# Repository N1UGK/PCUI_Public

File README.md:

# PCUI (Pocket Computer Universal Interface)
This is the official repo for firmware updates for the PCUI, owners manuals, and general information.  Further, this repo contains a collection of programs for various pocket computers and calculators supported by the PCUI.

## Development History

https://n1ugk.com/2025/12/pocket-computer-universal-interface/

## Features Summary

+ Provides cassette interface emulation to read and write programs and data directly to and from a micro SD card.
+ Provides a printer interface between the pocket computer or calculator and most standard “line printers” such as dot matrix, thermal receipt printers, serial, parallel, and Wi-Fi.
+ Supports printing of custom glyphs, including math, scientific and engineering symbols unique to each model.
+ Works independently without a computer and can be powered by a single 18650 lithium ion rechargeable battery.
+ OLED screen with user-friendly menu system and operating modes
+ Interface packs provide connectivity to each supported model, no need for OEM connection cables.
+ Updatable firmware and PC or Mac connectivity via USB for mounting micro SD card
+ Plotter emulation mode to provide printouts of plots using modern printers allowing programs which leveraged plotter features to be used on modern printers.
+ ASCII BASIC conversion to tokenized BASIC “on the fly”, allowing for program edits and program creation on a Mac or PC and directly sending it to a pocket computer.
+ Wi-Fi connectivity and web interface for program viewing, editing, UI control, printing, and status.
+ Online program library browsing and installing directly from GitHub allows you to view community released programs for various models of pocket computers directly from the PCUI.
+ True low-level cassette interface integration - byte level retrieval and storage of programs and data images, not just a simple "record" and "playback" mechanism.

## Supported Models

The following models are currently supported with more models in progress:

+ Texas Instruments	Graph Link Graphing Calculators
  + TI-82*, TI-85*, TI-86*, TI-89*, TI-92*, TI-92 Plus*, Voyage 200*
+ Sharp 9-pin “CE-121” / “CE-122” Compatibles
  + PC-1210, PC-1211, PC-1212, TRS-80 PC-1*
+ Sharp	Older 11-pin “CE-126P” Compatibles
  + PC-1245, PC-1246, PC-1246S, PC-1247, PC-1248, Tandy PC-8*
  + PC-1250, PC-1250A, PC-1251, PC-1251H, PC-1255, Tandy PC-3* and PC-3 A/B*, PC-1270
+ 11-pin “CE-126P” Compatibles
  + PC-1260, PC-1280
+ Sharp	Newer 11-pin “CE-126P” Compatibles
  + PC-1401, PC-1403*, PC-1421, PC-1430, PC-1450, EL-5500, EL-5500 II, EL-5500III*
+ Casio	12-pin PB-100 Series FP-12(S) Compatibles
  + PB-100, PB-110, PB-120, PB-200, PB-400, PB-410*, FX-700P, FX-710P, Tandy PC-4 Version B*, TRS-80 PC-4 Version A*
+ Casio	12-pin FX “Clamshell” Series
  + FX-770P, FX-780P, FX-781P, FX-785P, FX-790P, FX-791P, FX-795P, Tandy PC-5*, Tandy PC-6*
+ Casio	15-pin “FA-10” Compatibles
  + PB-700*, PB-770*
+ Casio	FX-702P*, FX-602P*

_*Tested and Verified, others should work since they use the same interface_

The PCUI Owners manual can be found in the [Documentation](./Documentation/) folder.

Firmware updates can be found in the [Firmware](./Firmware/) folder.

## Purchasing a Kit or Fully Assembled PCUI

A PCUI can be purchased as a kit or fully assembled.  

+ PCUI Kit - includes pre-flashed Pico 2 W, Main PCB and all components.  Interface pack kits are add-ons.  
  + Assembly instructions are located in the [Documentation](./Documentation/) folder.
  + The BOM, 3D model, KiCad Projects are located in the [Hardware](./Hardware/) folder.
+ PCUI Fully Assembled - includes a fully assembled PCUI and chosen interface pack add-ons.
+ To purchase a PCUI, <a href="https://www.tindie.com/products/n1ugk/pocket-computer-universal-interface-pcui/">click here</a>.

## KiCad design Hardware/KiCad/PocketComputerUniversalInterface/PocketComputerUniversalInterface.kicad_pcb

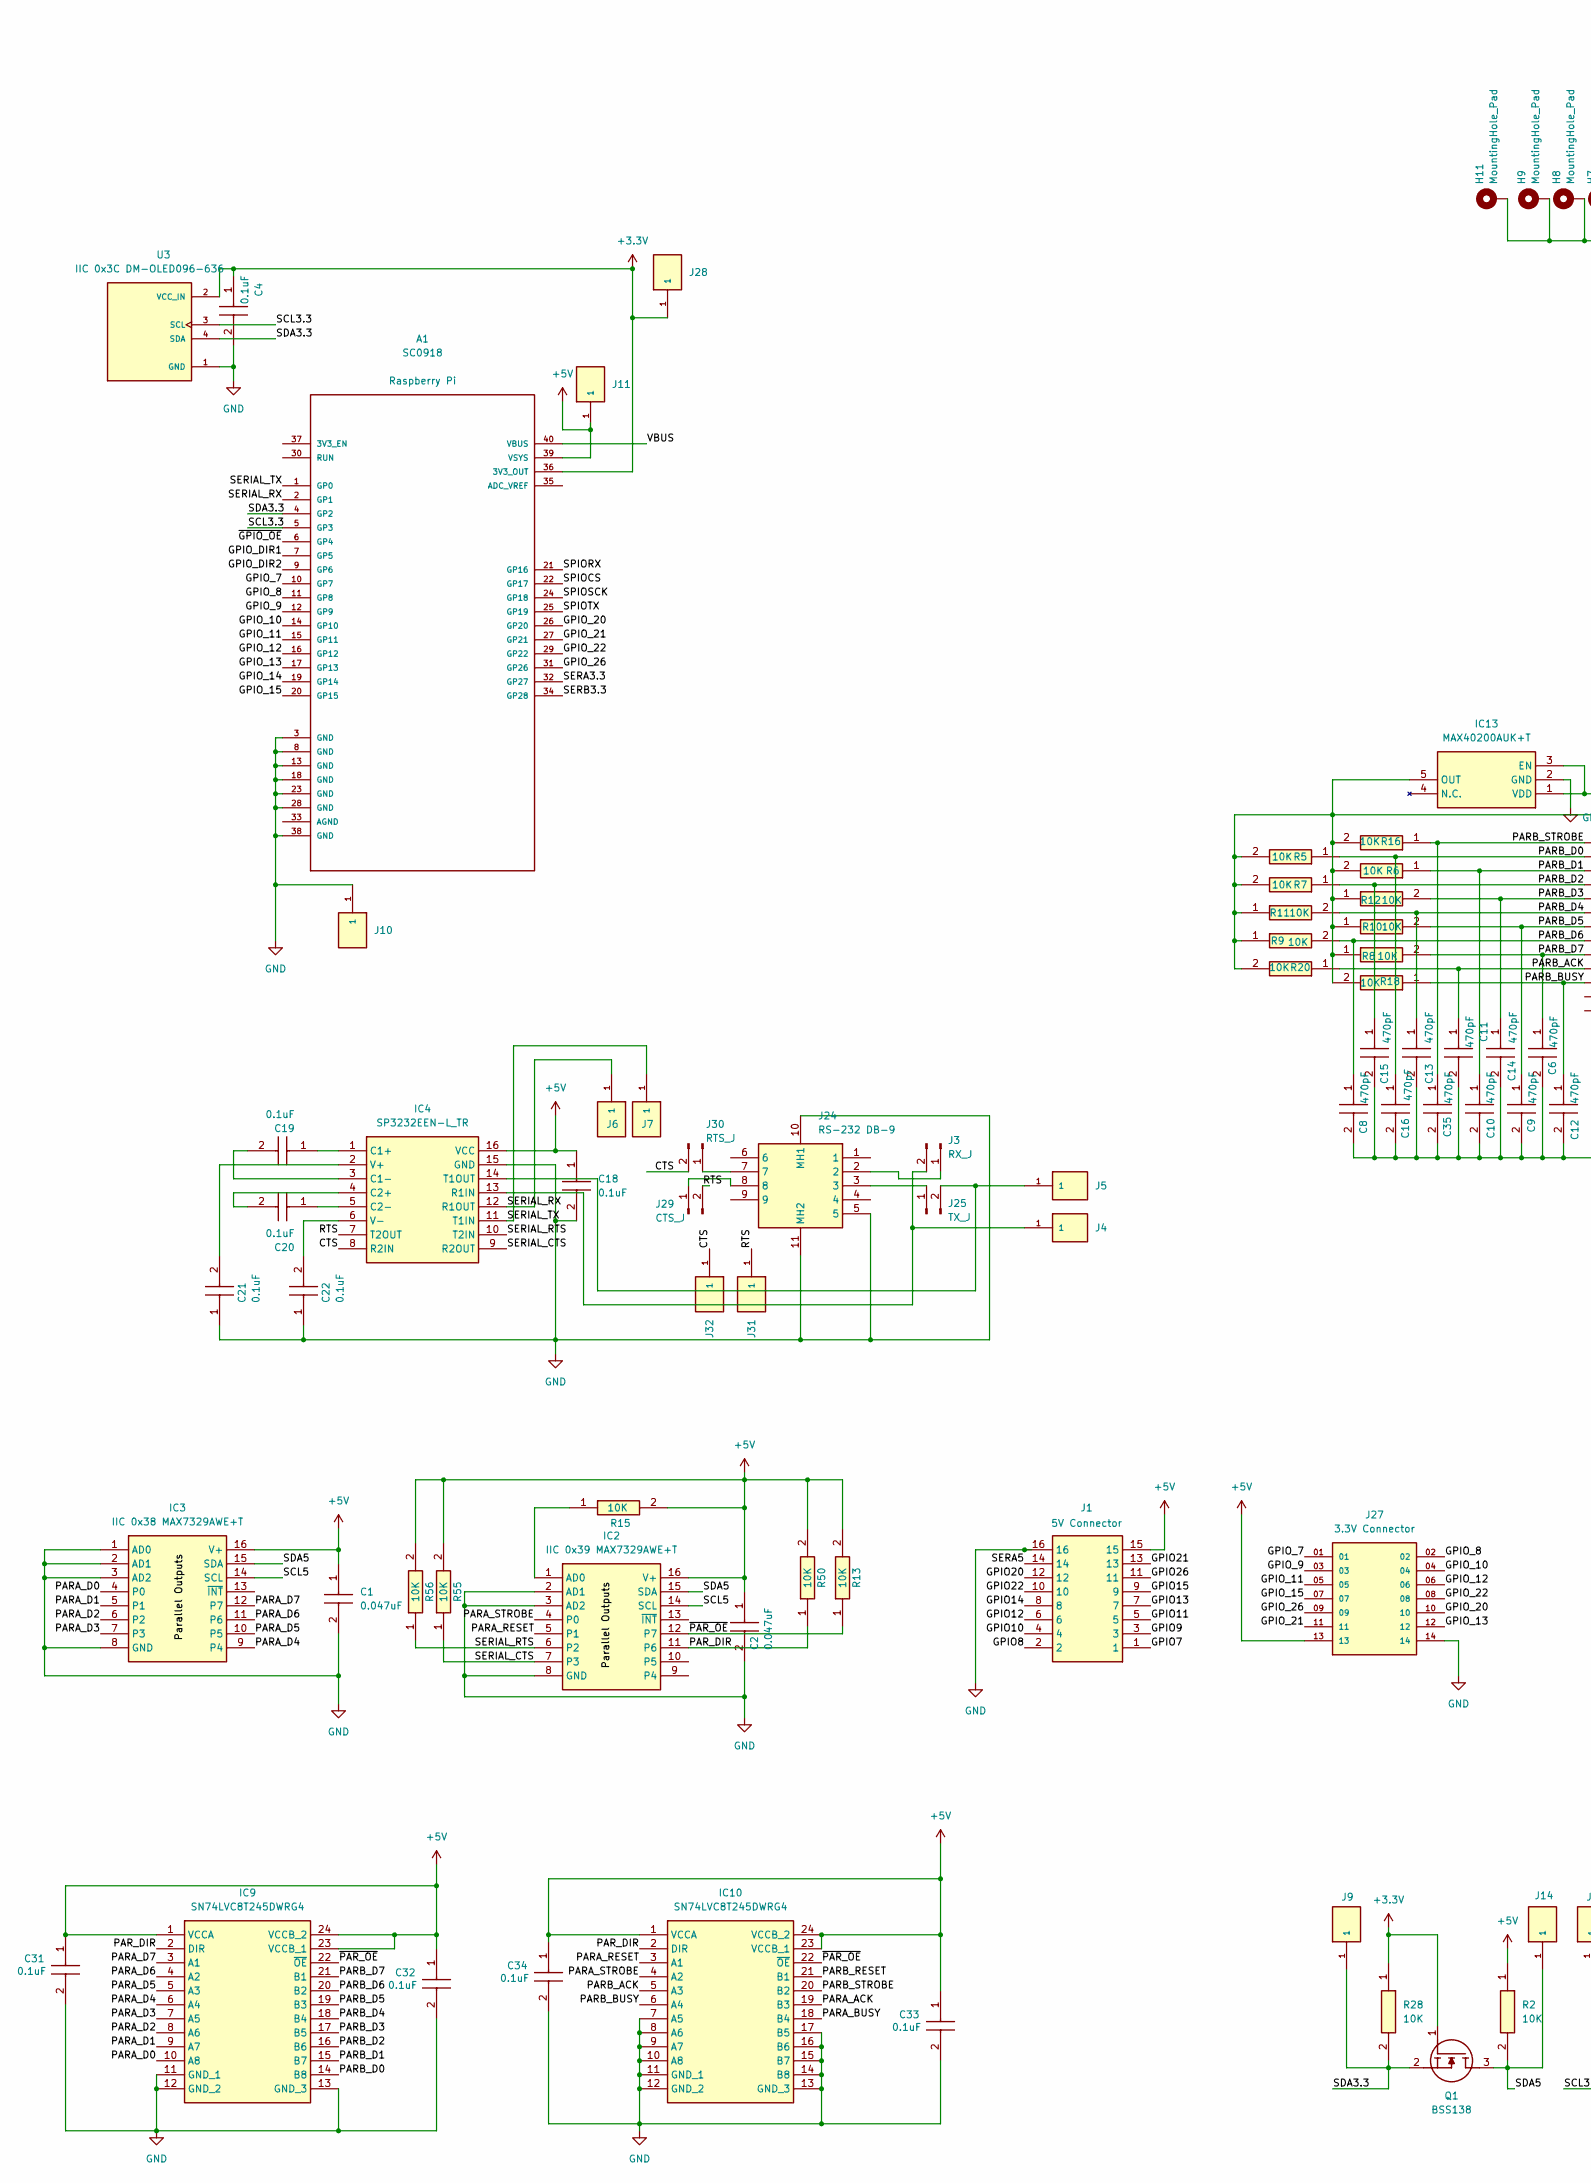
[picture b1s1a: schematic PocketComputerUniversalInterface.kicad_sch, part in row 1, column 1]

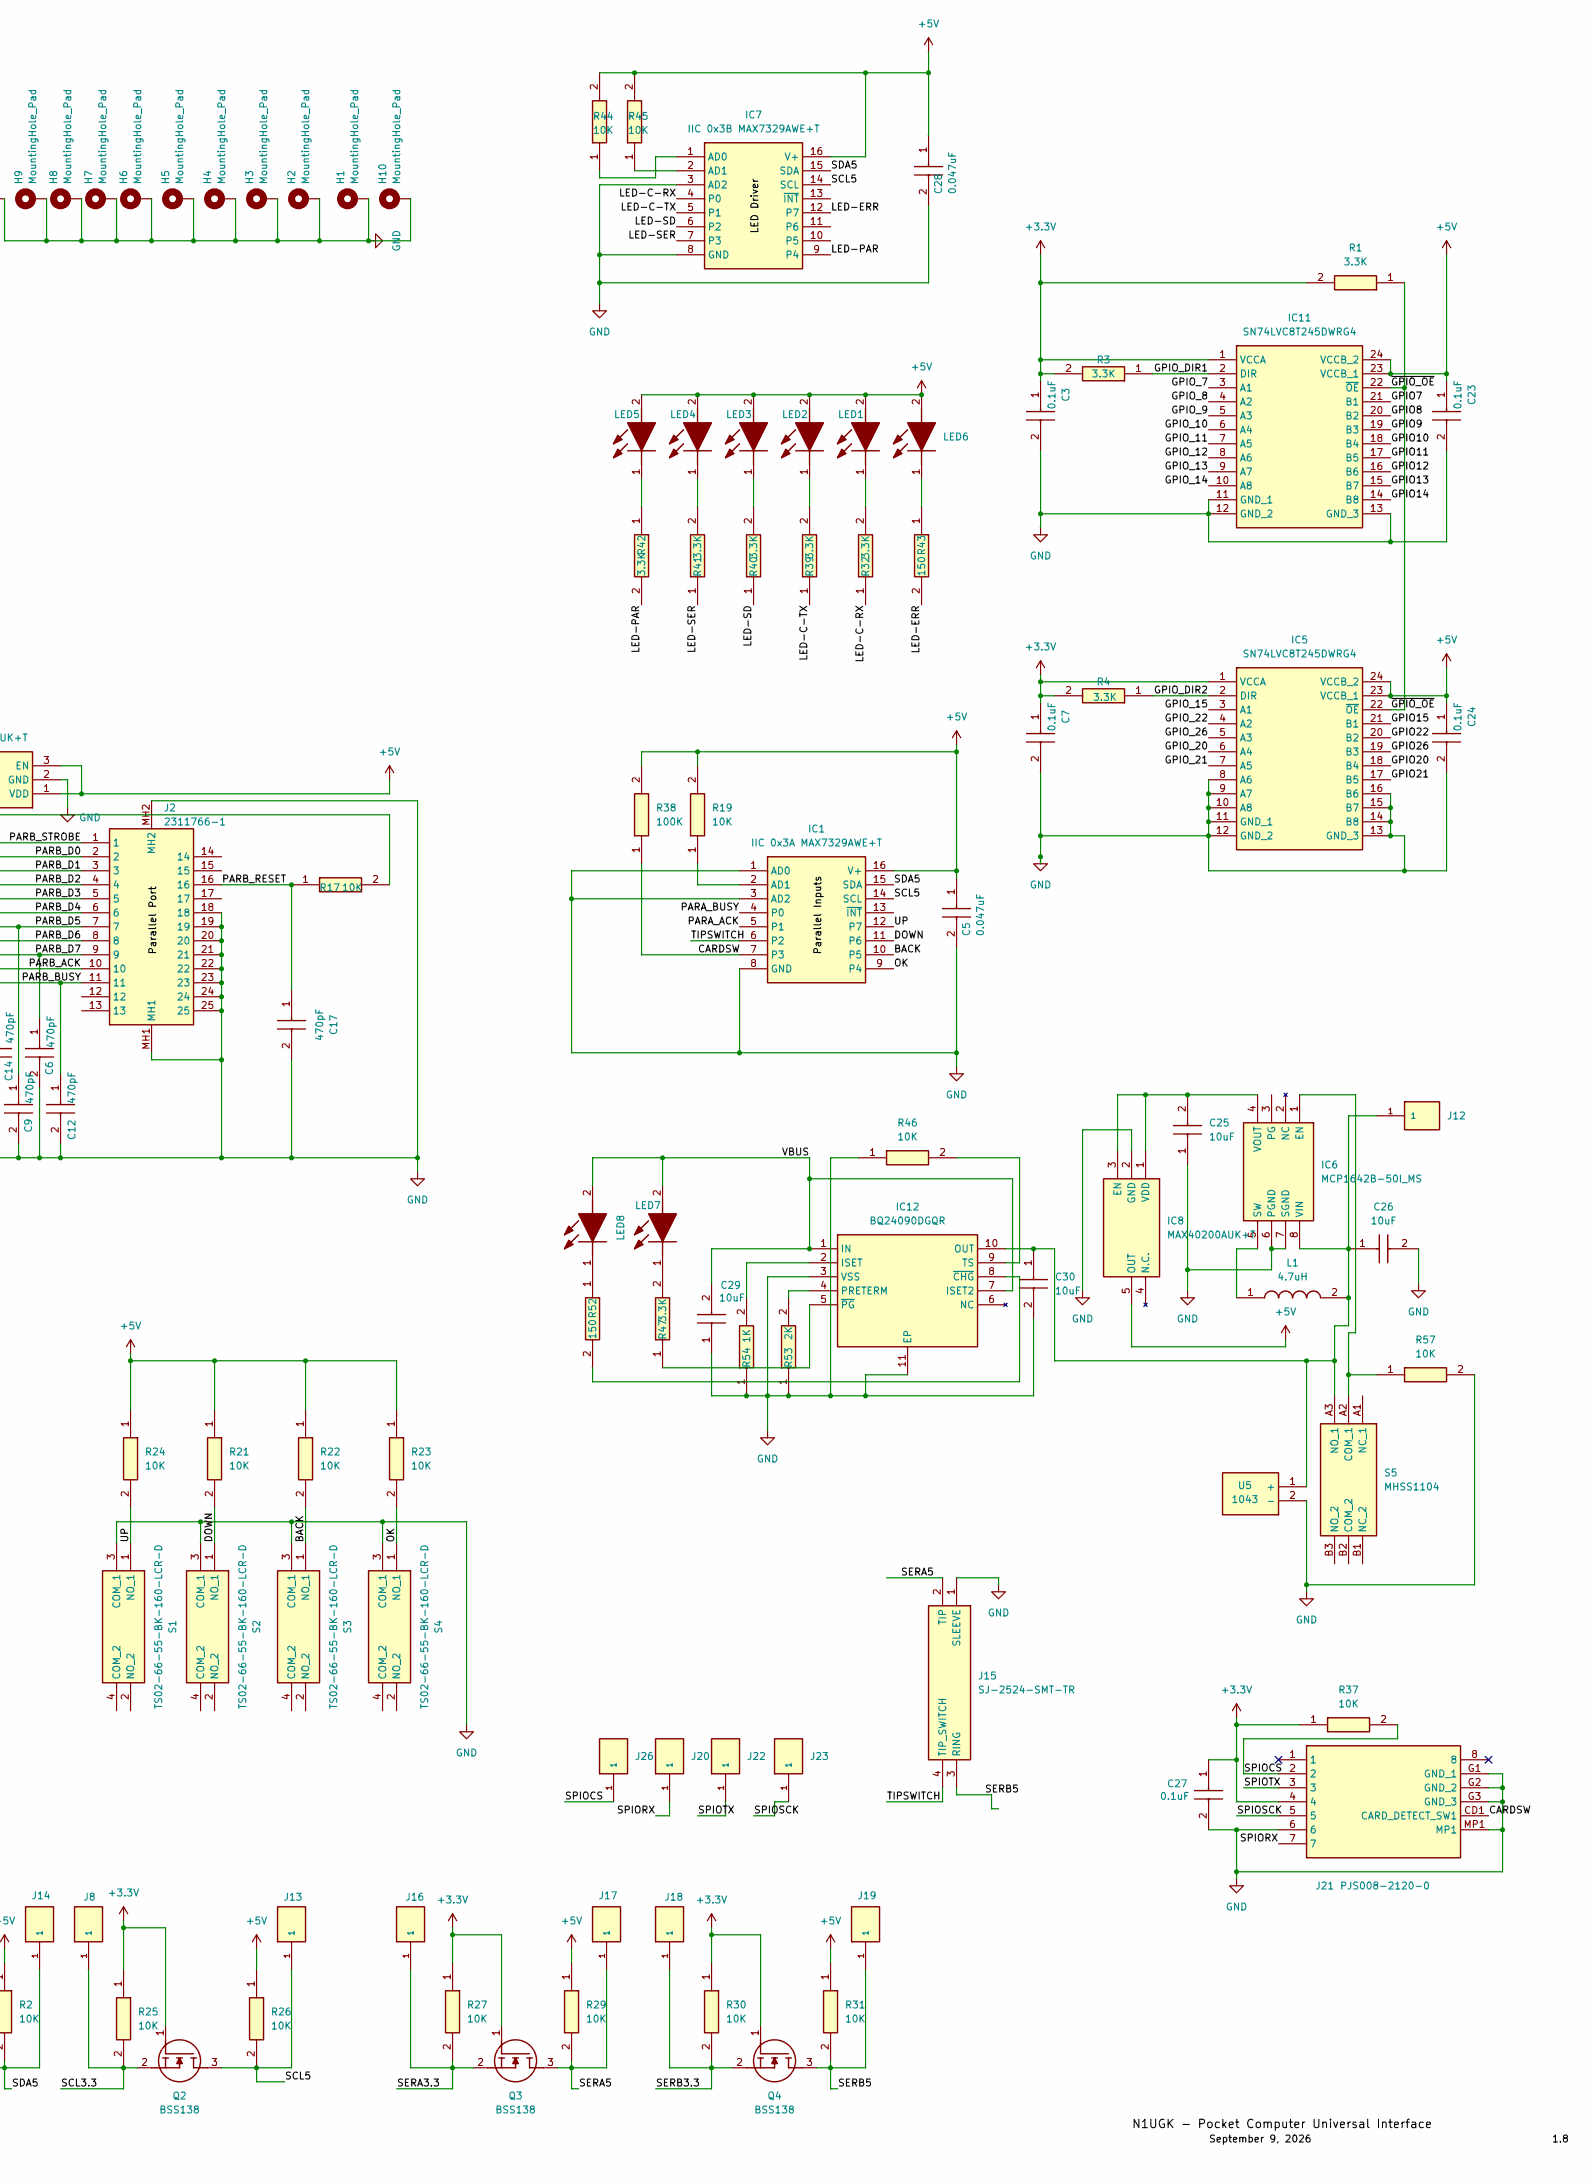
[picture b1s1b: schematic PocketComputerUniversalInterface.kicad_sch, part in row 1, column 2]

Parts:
A1: SC0918; MODULE_SC0918; PARTREV 1.6
C1, C2, C5, C28: 0.047uF; C1206; Mouser Part Number 80-C1206C473J5R
C3, C4, C7, C23, C24: 0.1uF; CAPC3216X94N; Mouser Part Number 581-12062A471KAT2A
C6, C8, C9, C10, C11, C12, C13, C14, C15, C16, C17, C35: 470pF; CAPC3216X94N; Mouser Part Number 581-12062A471KAT2A
C18, C19, C20, C21, C22, C27, C31, C32, C33, C34: 0.1uF; CAPC3216X94N; Mouser Part Number 581-12061C103J
C25, C26, C29, C30: 10uF; CAPC1608X90N; Mouser Part Number 81-GRM188R60J106ME4D
H1, H2, H3, H4, H5, H6, H7, H8, H9, H10, H11: MountingHole_Pad; MountingHole_3.2mm_M3_Pad_Via
IC1: IIC 0x3A MAX7329AWE+T; SOIC127P1032X265-16N; Mouser Part Number 700-MAX7329AWET
IC2: IIC 0x39 MAX7329AWE+T; SOIC127P1032X265-16N; Mouser Part Number 700-MAX7329AWET
IC3: IIC 0x38 MAX7329AWE+T; SOIC127P1032X265-16N; Mouser Part Number 700-MAX7329AWET
IC4: SP3232EEN-L_TR; SOIC127P600X175-16N; Mouser Part Number 701-SP3232EEN-L/TR
IC5, IC9, IC10, IC11: SN74LVC8T245DWRG4; SOIC127P1030X265-24N; Mouser Part Number 595-74LVC8T245DWRG4
IC6: MCP1642B-50I_MS; SOP65P490X110-8N; Mouser Part Number 579-MCP1642B-50I/MS
IC7: IIC 0x3B MAX7329AWE+T; SOIC127P1032X265-16N; Mouser Part Number 700-MAX7329AWET
IC8, IC13: MAX40200AUK+T; SOT95P280X145-5N; Mouser Part Number 700-MAX40200AUK+T
IC12: BQ24090DGQR; SOP50P490X110-11N; Mouser Part Number 595-BQ24090DGQR
J1: 5V Connector; TSS-108-XX-YYY-D; Manufacturer_Part_Number TSS-108-02-L-D
J2: 2311766-1; 23117661; Mouser Part Number 571-2311766-1
J3: RX_J; PinHeader_1x02_P2.54mm_Vertical
J4, J5, J6, J7, J8, J9, J10, J11, J12, J13, J14, J16, J17, J18, J19, J20, J22, J23, J26, J28, J31, J32: SAMTEC-HMTSW-101-24-X-S-290
J15: SJ-2524-SMT-TR; SJ2524SMTTR; Mouser Part Number 490-SJ-2524-SMT-TR
J21: PJS008-2120-0; PJS00821200; Mouser Part Number 945-PJS008-2120-0
J24: RS-232 DB-9; 6E17C009PBF221; Manufacturer_Part_Number 6E17C009PBF221
J25: TX_J; PinHeader_1x02_P2.54mm_Vertical
J27: 3.3V Connector; SAMTEC_TSS-107-02-H-D; PARTREV R
J29: CTS_J; PinHeader_1x02_P2.54mm_Vertical
J30: RTS_J; PinHeader_1x02_P2.54mm_Vertical
L1: 4.7uH; EPL3015472MLC; Mouser Part Number 994-EPL3015-472MLC
LED1, LED2, LED3, LED4, LED5, LED7: HSMM-A100-S00J1; LEDM3528X200N; Mouser Part Number 630-HSMM-A100-S00J1
LED6, LED8: HSMS-A100-L00J1; HSMSA100L00J1; Mouser Part Number 630-HSMS-A100-L00J1
Q1, Q2, Q3, Q4: BSS138; SOT95P240X120-3N; Mouser Part Number 512-BSS138
R1, R3, R4, R32, R39, R40, R41, R42, R47: 3.3K; RESC2013X65N; Mouser Part Number 756-WCR0805-10KFI
R2, R5, R6, R7, R8, R9, R10, R11, R12, R13, R15, R16, R17, R18, R19, R20, R21, R22, R23, R24, R25, R26, R27, R28, R29, R30, R31, R37, R44, R45, R46, R50, R55, R56, R57: 10K; RESC2013X65N; Mouser Part Number 756-WCR0805-10KFI
R38: 100K; RESC2013X65N; Mouser Part Number 756-WCR0805-10KFI
R43, R52: 150; RESC2013X65N; Mouser Part Number 756-WCR0805-10KFI
R53: 2K; RESC2013X65N; Mouser Part Number 756-WCR0805-10KFI
R54: 1K; RESC2013X65N; Mouser Part Number 756-WCR0805-10KFI
S1, S2, S3, S4: TS02-66-55-BK-160-LCR-D; TS026655BK160LCRD; Mouser Part Number 179-TS026655BK160LCR
S5: MHSS1104; Mouser Part Number 642-MHSS1104
U3: IIC 0x3C DM-OLED096-636; MODULE_DM-OLED096-636; PARTREV 2018-09-10
U5: 1043; Mouser Part Number 534-1043

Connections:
+3.3V: A1.36 (3V3_OUT), C3.1 (C1), C4.1, C7.1 (C1), C27.1 (C1), IC5.1 (VCCA), IC11.1 (VCCA), J21.4, J28.1, Q1.1 (G), Q2.1 (G), Q3.1 (G), Q4.1 (G), R1.2, R3.2, R4.2, R25.1, R27.1, R28.1, R30.1, R37.1, U3.2 (VCC_IN)
+5V: A1.39 (VSYS), C1.1, C2.1, C5.1, C18.1 (C1), C23.1 (C1), C24.1 (C1), C28.1, C31.1 (C1), C32.1 (C1), C33.1 (C1), C34.1 (C1), IC1.16 (V+), IC2.16 (V+), IC3.16 (V+), IC4.16 (VCC), IC5.23 (VCCB_1), IC5.24 (VCCB_2), IC7.16 (V+), IC8.5 (OUT), IC9.1 (VCCA), IC9.23 (VCCB_1), IC9.24 (VCCB_2), IC10.1 (VCCA), IC10.23 (VCCB_1), IC10.24 (VCCB_2), IC11.23 (VCCB_1), IC11.24 (VCCB_2), IC13.1 (VDD), IC13.3 (EN), J1.15, J11.1, J27.13, LED1.2 (A), LED2.2 (A), LED3.2 (A), LED4.2 (A), LED5.2 (A), LED6.2 (A), R2.1, R13.2, R15.2, R19.2, R21.1, R22.1, R23.1, R24.1, R26.1, R29.1, R31.1, R38.2, R44.2, R45.2, R50.2, R55.2, R56.2
/BACK: IC1.10 (P5), R22.2, S3.1 (NO_1)
/CARDSW: IC1.7 (P3), J21.CD1 (CARD_DETECT_SW1), R38.1
/CTS: IC4.8 (R2IN), J30.2, J32.1
/DOWN: IC1.11 (P6), R21.2, S2.1 (NO_1)
/GPIO7: IC11.21 (B1), J1.1
/GPIO8: IC11.20 (B2), J1.2
/GPIO9: IC11.19 (B3), J1.3
/GPIO10: IC11.18 (B4), J1.4
/GPIO11: IC11.17 (B5), J1.5
/GPIO12: IC11.16 (B6), J1.6
/GPIO13: IC11.15 (B7), J1.7
/GPIO14: IC11.14 (B8), J1.8
/GPIO15: IC5.21 (B1), J1.9
/GPIO20: IC5.18 (B4), J1.12
/GPIO21: IC5.17 (B5), J1.13
/GPIO22: IC5.20 (B2), J1.10
/GPIO26: IC5.19 (B3), J1.11
/GPIO_7: A1.10 (GP7), IC11.3 (A1), J27.01
/GPIO_8: A1.11 (GP8), IC11.4 (A2), J27.02
/GPIO_9: A1.12 (GP9), IC11.5 (A3), J27.03
/GPIO_10: A1.14 (GP10), IC11.6 (A4), J27.04
/GPIO_11: A1.15 (GP11), IC11.7 (A5), J27.05
/GPIO_12: A1.16 (GP12), IC11.8 (A6), J27.06
/GPIO_13: A1.17 (GP13), IC11.9 (A7), J27.12
/GPIO_14: A1.19 (GP14), IC11.10 (A8)
/GPIO_15: A1.20 (GP15), IC5.3 (A1), J27.07
/GPIO_20: A1.26 (GP20), IC5.6 (A4), J27.10
/GPIO_21: A1.27 (GP21), IC5.7 (A5), J27.11
/GPIO_22: A1.29 (GP22), IC5.4 (A2), J27.08
/GPIO_26: A1.31 (GP26), IC5.5 (A3), J27.09
/GPIO_DIR1: A1.7 (GP5), IC11.2 (DIR), R3.1
/GPIO_DIR2: A1.9 (GP6), IC5.2 (DIR), R4.1
/LED-C-RX: IC7.4 (P0), R32.1
/LED-C-TX: IC7.5 (P1), R39.1
/LED-ERR: IC7.12 (P7), R43.2
/LED-PAR: IC7.9 (P4), R42.2
/LED-SD: IC7.6 (P2), R40.1
/LED-SER: IC7.7 (P3), R41.1
/OK: IC1.9 (P4), R23.2, S4.1 (NO_1)
/PARA_ACK: IC1.5 (P1), IC10.19 (B3)
/PARA_BUSY: IC1.4 (P0), IC10.18 (B4)
/PARA_D0: IC3.4 (P0), IC9.10 (A8)
/PARA_D1: IC3.5 (P1), IC9.9 (A7)
/PARA_D2: IC3.6 (P2), IC9.8 (A6)
/PARA_D3: IC3.7 (P3), IC9.7 (A5)
/PARA_D4: IC3.9 (P4), IC9.6 (A4)
/PARA_D5: IC3.10 (P5), IC9.5 (A3)
/PARA_D6: IC3.11 (P6), IC9.4 (A2)
/PARA_D7: IC3.12 (P7), IC9.3 (A1)
/PARA_RESET: IC2.5 (P1), IC10.3 (A1)
/PARA_STROBE: IC2.4 (P0), IC10.4 (A2)
/PARB_ACK: C11.1 (C1), IC10.5 (A3), J2.10, R20.1
/PARB_BUSY: C12.1 (C1), IC10.6 (A4), J2.11, R18.1
/PARB_D0: C16.1 (C1), IC9.14 (B8), J2.2, R5.1
/PARB_D1: C10.1 (C1), IC9.15 (B7), J2.3, R6.1
/PARB_D2: C15.1 (C1), IC9.16 (B6), J2.4, R7.1
/PARB_D3: C14.1 (C1), IC9.17 (B5), J2.5, R12.2
/PARB_D4: C13.1 (C1), IC9.18 (B4), J2.6, R11.2
/PARB_D5: C9.1 (C1), IC9.19 (B3), J2.7, R10.2
/PARB_D6: C8.1 (C1), IC9.20 (B2), J2.8, R9.2
/PARB_D7: C6.1 (C1), IC9.21 (B1), J2.9, R8.2
/PARB_RESET: C17.1 (C1), IC10.21 (B1), J2.16, R17.1
/PARB_STROBE: C35.1 (C1), IC10.20 (B2), J2.1, R16.1
/PAR_DIR: IC2.11 (P6), IC9.2 (DIR), IC10.2 (DIR), R50.1
/RTS: IC4.7 (T2OUT), J29.2, J31.1
/SCL3.3: A1.5 (GP3), J8.1, Q2.2 (S), R25.2, U3.3 (SCL)
/SCL5: IC1.14 (SCL), IC2.14 (SCL), IC3.14 (SCL), IC7.14 (SCL), J13.1, Q2.3 (D), R26.2
/SDA3.3: A1.4 (GP2), J9.1, Q1.2 (S), R28.2, U3.4 (SDA)
/SDA5: IC1.15 (SDA), IC2.15 (SDA), IC3.15 (SDA), IC7.15 (SDA), J14.1, Q1.3 (D), R2.2
/SERA3.3: A1.32 (GP27), J16.1, Q3.2 (S), R27.2
/SERA5: J1.14, J15.2 (TIP), J17.1, Q3.3 (D), R29.2
/SERB3.3: A1.34 (GP28), J18.1, Q4.2 (S), R30.2
/SERB5: J15.3 (RING), J19.1, Q4.3 (D), R31.2
/SERIAL_CTS: IC2.7 (P3), IC4.9 (R2OUT), R55.1
/SERIAL_RTS: IC2.6 (P2), IC4.10 (T2IN), R56.1
/SERIAL_RX: A1.2 (GP1), IC4.12 (R1OUT), J6.1
/SERIAL_TX: A1.1 (GP0), IC4.11 (T1IN), J7.1
/SPIOCS: A1.22 (GP17), J21.2, J26.1, R37.2
/SPIORX: A1.21 (GP16), J20.1, J21.7
/SPIOSCK: A1.24 (GP18), J21.5, J23.1
/SPIOTX: A1.25 (GP19), J21.3, J22.1
/TIPSWITCH: IC1.6 (P2), J15.4 (TIP_SWITCH)
/UP: IC1.12 (P7), R24.2, S1.1 (NO_1)
/VBUS: A1.40 (VBUS), C29.2, IC12.1 (IN), IC12.7 (ISET2), LED7.2 (A), LED8.2 (A)
/~GPIO_OE: A1.6 (GP4), IC5.22 (~OE), IC11.22 (~OE), R1.1
/~PAR_OE: IC2.12 (P7), IC9.22 (~OE), IC10.22 (~OE), R13.1
GND: A1.3 (GND), A1.8 (GND), A1.13 (GND), A1.18 (GND), A1.23 (GND), A1.28 (GND), A1.38 (GND), C1.2, C2.2, C3.2 (C2), C4.2, C5.2, C6.2 (C2), C7.2 (C2), C8.2 (C2), C9.2 (C2), C10.2 (C2), C11.2 (C2), C12.2 (C2), C13.2 (C2), C14.2 (C2), C15.2 (C2), C16.2 (C2), C17.2 (C2), C18.2 (C2), C21.1 (C1), C22.1 (C1), C23.2 (C2), C24.2 (C2), C25.1, C26.2, C27.2 (C2), C28.2, C29.1, C30.2, C31.2 (C2), C32.2 (C2), C33.2 (C2), C34.2 (C2), C35.2 (C2), H1.1, H2.1, H3.1, H4.1, H5.1, H6.1, H7.1, H8.1, H9.1, H10.1, H11.1, IC1.1 (AD0), IC1.3 (AD2), IC1.8 (GND), IC2.2 (AD1), IC2.3 (AD2), IC2.8 (GND), IC3.1 (AD0), IC3.2 (AD1), IC3.3 (AD2), IC3.8 (GND), IC4.15 (GND), IC5.8 (A6), IC5.9 (A7), IC5.10 (A8), IC5.11 (GND_1), IC5.12 (GND_2), IC5.13 (GND_3), IC5.14 (B8), IC5.15 (B7), IC5.16 (B6), IC6.6 (PGND), IC6.7 (SGND), IC7.3 (AD2), IC7.8 (GND), IC8.2 (GND), IC9.11 (GND_1), IC9.12 (GND_2), IC9.13 (GND_3), IC10.7 (A5), IC10.8 (A6), IC10.9 (A7), IC10.10 (A8), IC10.11 (GND_1), IC10.12 (GND_2), IC10.13 (GND_3), IC10.14 (B8), IC10.15 (B7), IC10.16 (B6), IC10.17 (B5), IC11.11 (GND_1), IC11.12 (GND_2), IC11.13 (GND_3), IC12.3 (VSS), IC12.11 (EP), IC13.2 (GND), J1.16, J2.18, J2.19, J2.20, J2.21, J2.22, J2.23, J2.24, J2.25, J2.MH1, J2.MH2, J10.1, J15.1 (SLEEVE), J21.6, J21.G1 (GND_1), J21.G2 (GND_2), J21.G3 (GND_3), J21.MP1, J24.5, J24.10 (MH1), J24.11 (MH2), J27.14, R46.1, R53.1, R54.1, R57.2, S1.3 (COM_1), S2.3 (COM_1), S3.3 (COM_1), S4.3 (COM_1), U3.1 (GND), U5.2 (-)
unnamed: C19.1 (C1), IC4.1 (C1+)
unnamed: C19.2 (C2), IC4.3 (C1-)
unnamed: C20.1 (C1), IC4.5 (C2-)
unnamed: C20.2 (C2), IC4.4 (C2+)
unnamed: C21.2 (C2), IC4.2 (V+)
unnamed: C22.2 (C2), IC4.6 (V-)
unnamed: IC1.2 (AD1), R19.1
unnamed: IC2.1 (AD0), R15.1
unnamed: IC4.13 (R1IN), J3.2, J4.1
unnamed: IC4.14 (T1OUT), J5.1, J25.2
unnamed: IC6.1 (EN), R57.1, S5.A2 (COM_1)
unnamed: IC6.5 (SW), L1.1
unnamed: C25.2, IC6.4 (VOUT), IC8.1 (VDD), IC8.3 (EN)
unnamed: IC7.1 (AD0), R44.1
unnamed: IC7.2 (AD1), R45.1
unnamed: IC12.2 (ISET), R54.2
unnamed: C26.1, C30.1, IC6.8 (VIN), IC12.10 (OUT), J12.1, L1.2, S5.A3 (NO_1), U5.1 (+)
unnamed: IC12.4 (PRETERM), R53.2
unnamed: IC12.9 (TS), R46.2
unnamed: IC12.8 (~CHG), R52.2
unnamed: IC12.5 (~PG), R47.1
unnamed: IC13.5 (OUT), R5.2, R6.2, R7.2, R8.1, R9.1, R10.1, R11.1, R12.1, R16.2, R17.2, R18.2, R20.2
unnamed: J3.1, J24.2
unnamed: J24.3, J25.1
unnamed: J24.8, J29.1
unnamed: J24.7, J30.1
unnamed: LED1.1 (K), R32.2
unnamed: LED2.1 (K), R39.2
unnamed: LED3.1 (K), R40.2
unnamed: LED4.1 (K), R41.2
unnamed: LED5.1 (K), R42.1
unnamed: LED6.1 (K), R43.1
unnamed: LED7.1 (K), R47.2
unnamed: LED8.1 (K), R52.1

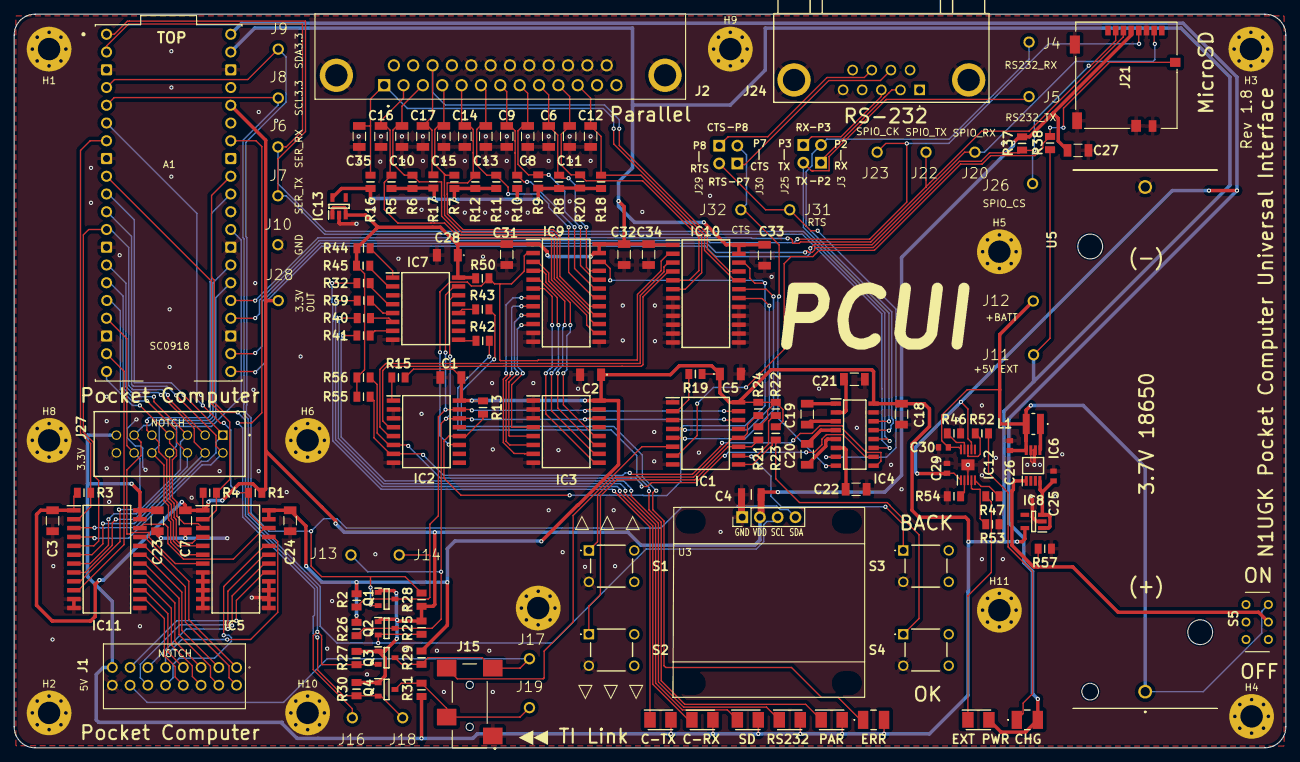
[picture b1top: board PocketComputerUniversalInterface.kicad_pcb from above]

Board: 2 copper layers, 182.0 x 105.0 mm, 161 parts (0 on the bottom side), 123 nets.

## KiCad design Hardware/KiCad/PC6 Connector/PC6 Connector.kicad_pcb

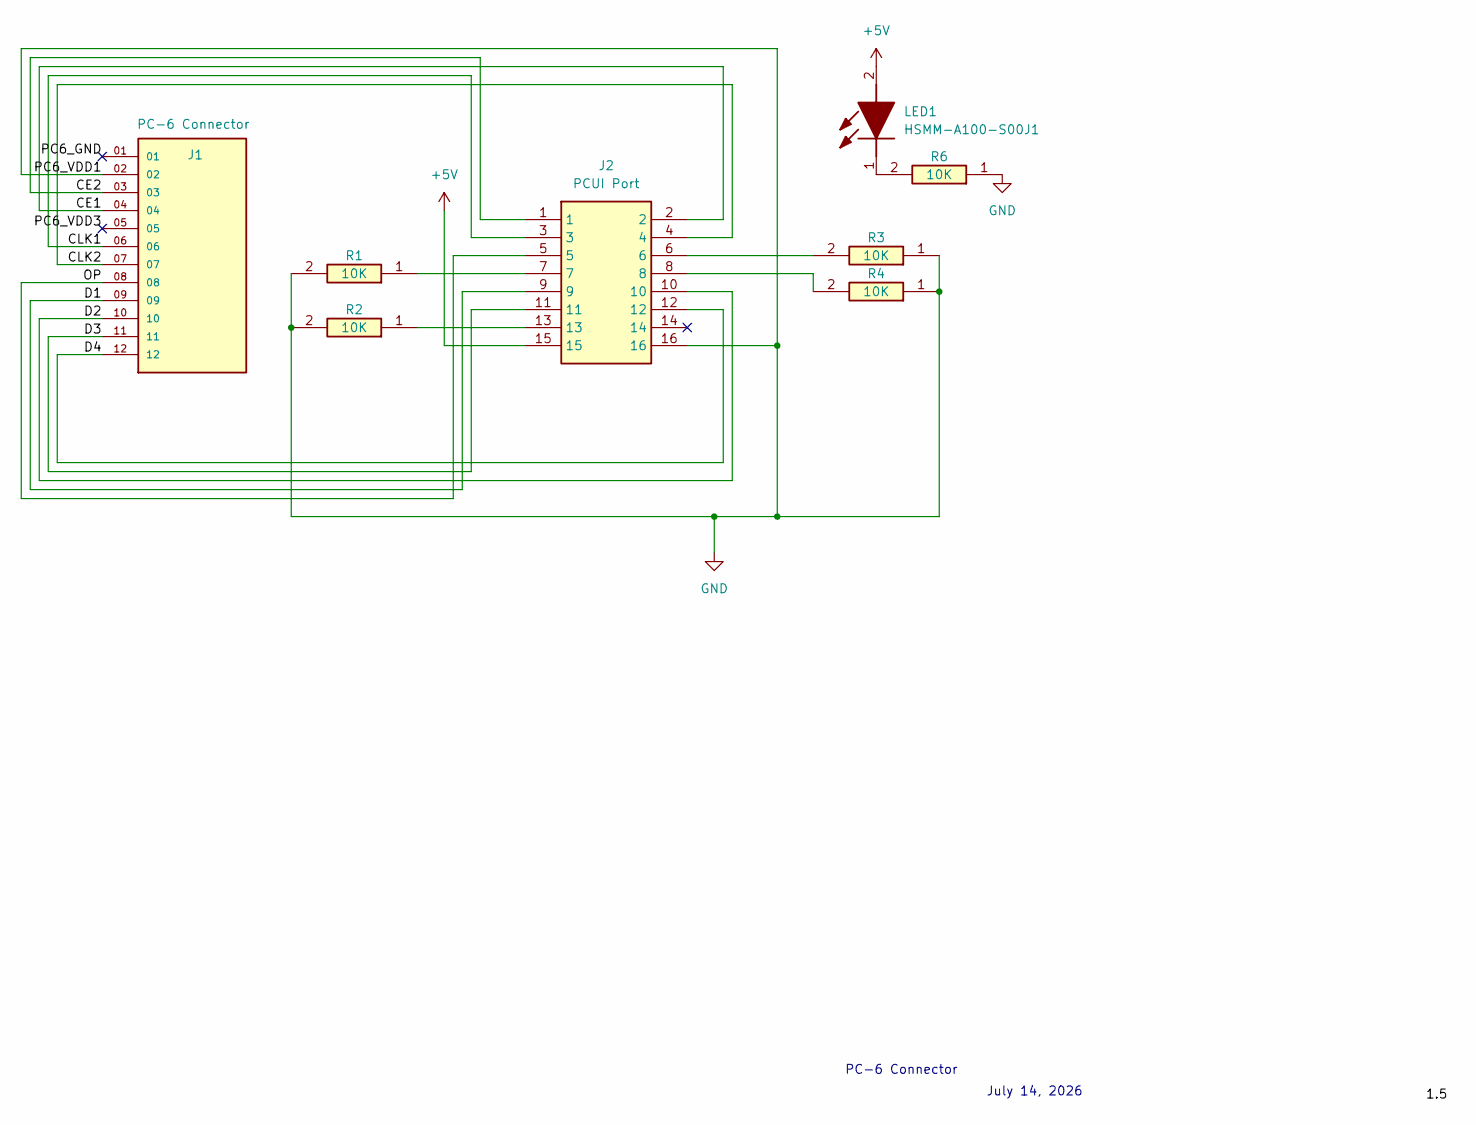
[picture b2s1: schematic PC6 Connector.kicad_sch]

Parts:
J1: PC-6 Connector; SAMTEC_TSW-112-07-L-S-LL; PARTREV R
J2: PCUI Port; TSS-108-XX-YYY-D; Manufacturer_Part_Number TSS-108-02-L-D
LED1: HSMM-A100-S00J1; LEDM3528X200N; Mouser Part Number 630-HSMM-A100-S00J1
R1, R2, R3, R4, R6: 10K; RESC2013X65N; Mouser Part Number 756-WCR0805-10KFI

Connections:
+5V: J2.15, LED1.2 (A)
/CE1: J1.04, J2.2
/CE2: J1.03, J2.1
/CLK1: J1.06, J2.3
/CLK2: J1.07, J2.4
/D1: J1.09, J2.9
/D2: J1.10, J2.10
/D3: J1.11, J2.11
/D4: J1.12, J2.12
/OP: J1.08, J2.5
/PC6_GND: J1.01
/PC6_VDD3: J1.05
GND: J1.02, J2.16, R1.2, R2.2, R3.1, R4.1, R6.1
unnamed: J2.6, R3.2
unnamed: J2.7, R1.1
unnamed: J2.8, R4.2
unnamed: J2.13, R2.1
unnamed: LED1.1 (K), R6.2

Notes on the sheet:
July 14, 2026
PC-6 Connector

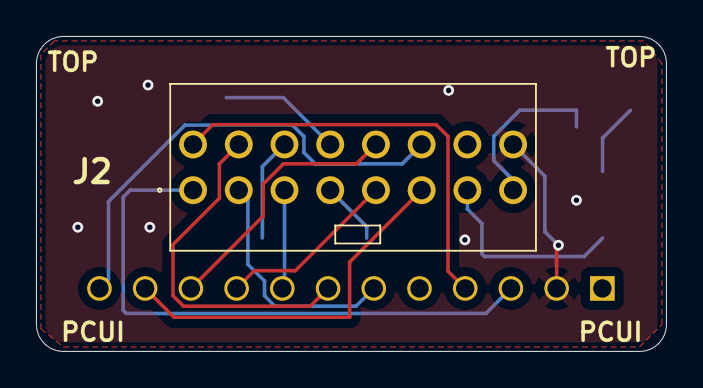
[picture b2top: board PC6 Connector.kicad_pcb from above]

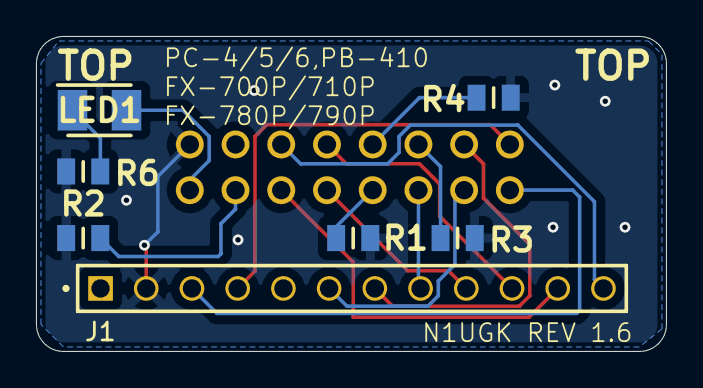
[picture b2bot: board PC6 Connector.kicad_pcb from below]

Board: 2 copper layers, 35.0 x 17.5 mm, 8 parts (7 on the bottom side), 16 nets.

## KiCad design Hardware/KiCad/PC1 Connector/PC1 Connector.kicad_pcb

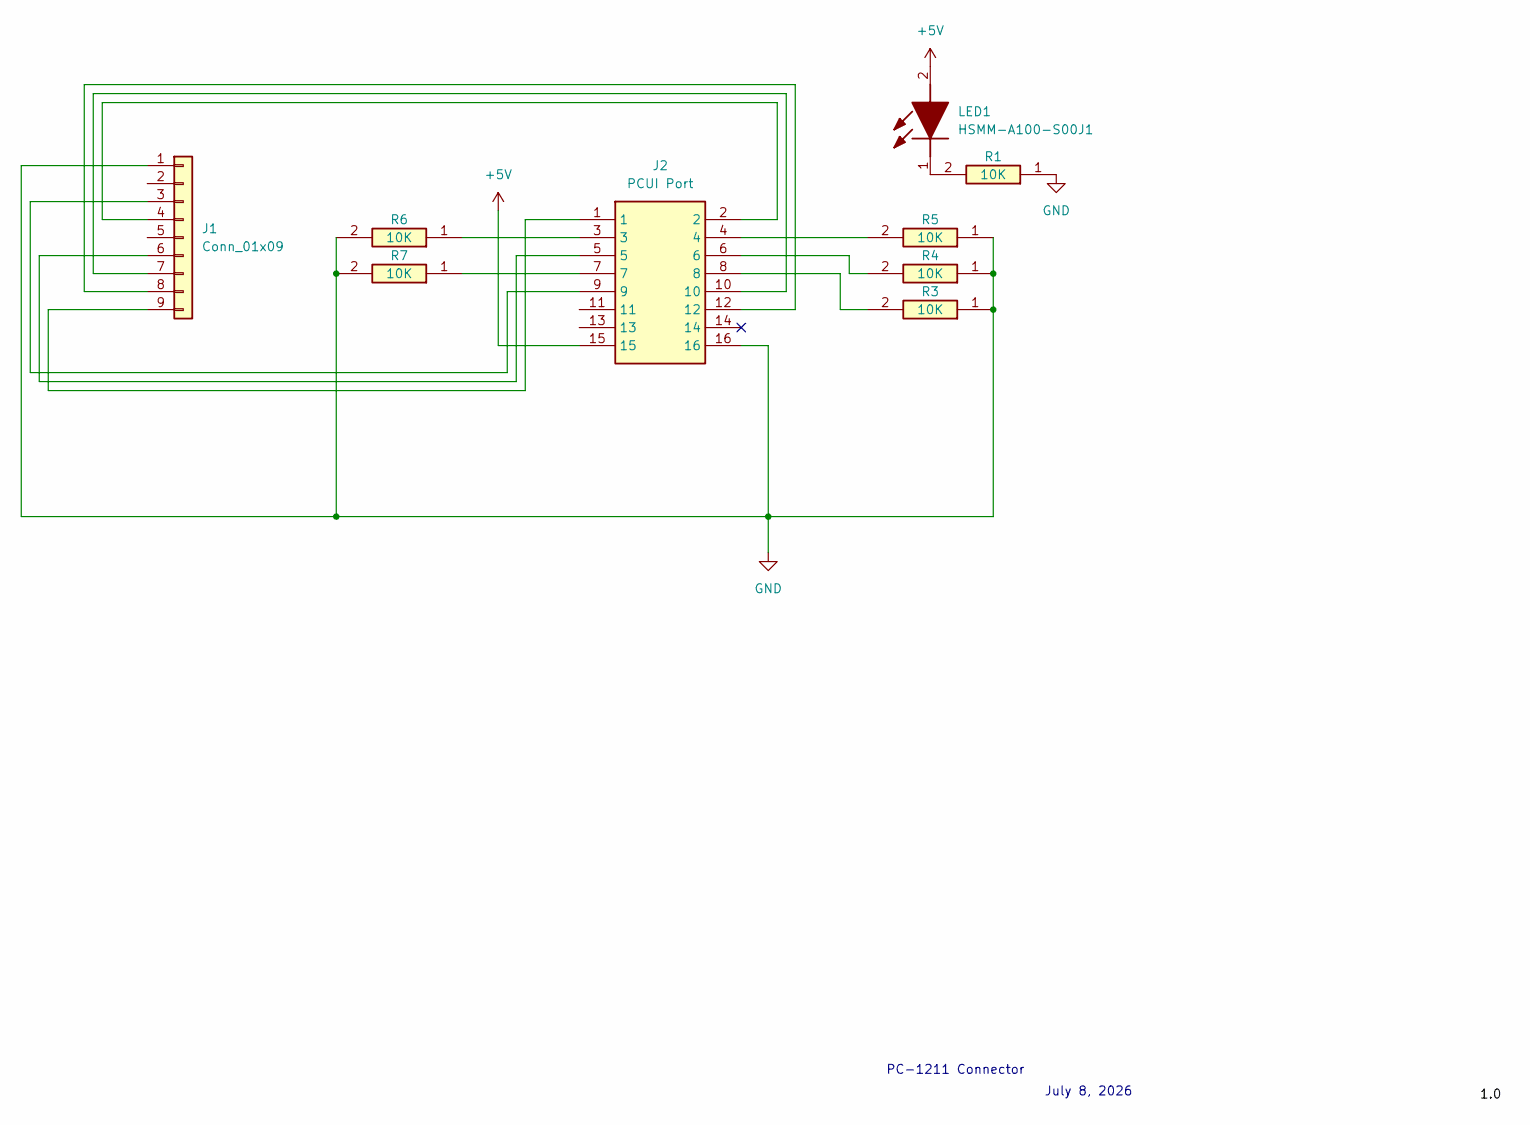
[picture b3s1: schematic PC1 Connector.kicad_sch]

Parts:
J1: Conn_01x09; PinHeader_1x09_P2.54mm_Vertical
J2: PCUI Port; TSS-108-XX-YYY-D; Manufacturer_Part_Number TSS-108-02-L-D
LED1: HSMM-A100-S00J1; LEDM3528X200N; Mouser Part Number 630-HSMM-A100-S00J1
R1, R3, R4, R5, R6, R7: 10K; RESC2013X65N; Mouser Part Number 756-WCR0805-10KFI

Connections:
+5V: J2.15, LED1.2 (A)
GND: J1.1, J2.16, R1.1, R3.1, R4.1, R5.1, R6.2, R7.2
unnamed: J1.3, J2.9
unnamed: J1.4, J2.2
unnamed: J1.6, J2.5
unnamed: J1.7, J2.10
unnamed: J1.8, J2.12
unnamed: J1.9, J2.1
unnamed: J2.3, R6.1
unnamed: J2.4, R5.2
unnamed: J2.6, R4.2
unnamed: J2.7, R7.1
unnamed: J2.8, R3.2
unnamed: LED1.1 (K), R1.2

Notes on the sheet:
July 8, 2026
PC-1211 Connector

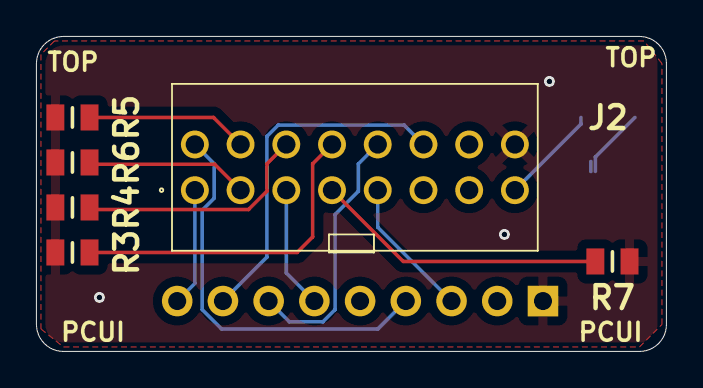
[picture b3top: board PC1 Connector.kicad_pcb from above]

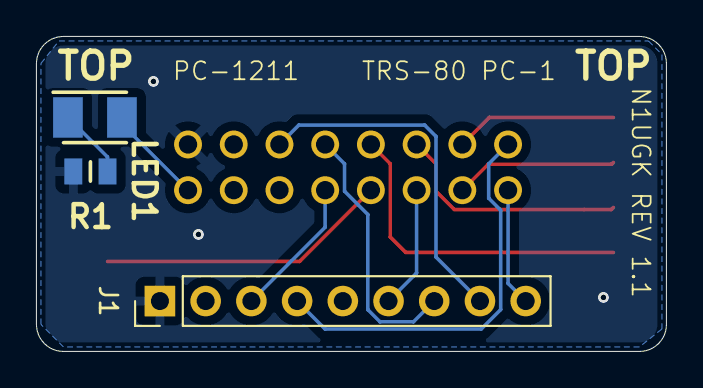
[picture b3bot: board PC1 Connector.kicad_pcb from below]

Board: 2 copper layers, 35.0 x 17.5 mm, 9 parts (3 on the bottom side), 14 nets.

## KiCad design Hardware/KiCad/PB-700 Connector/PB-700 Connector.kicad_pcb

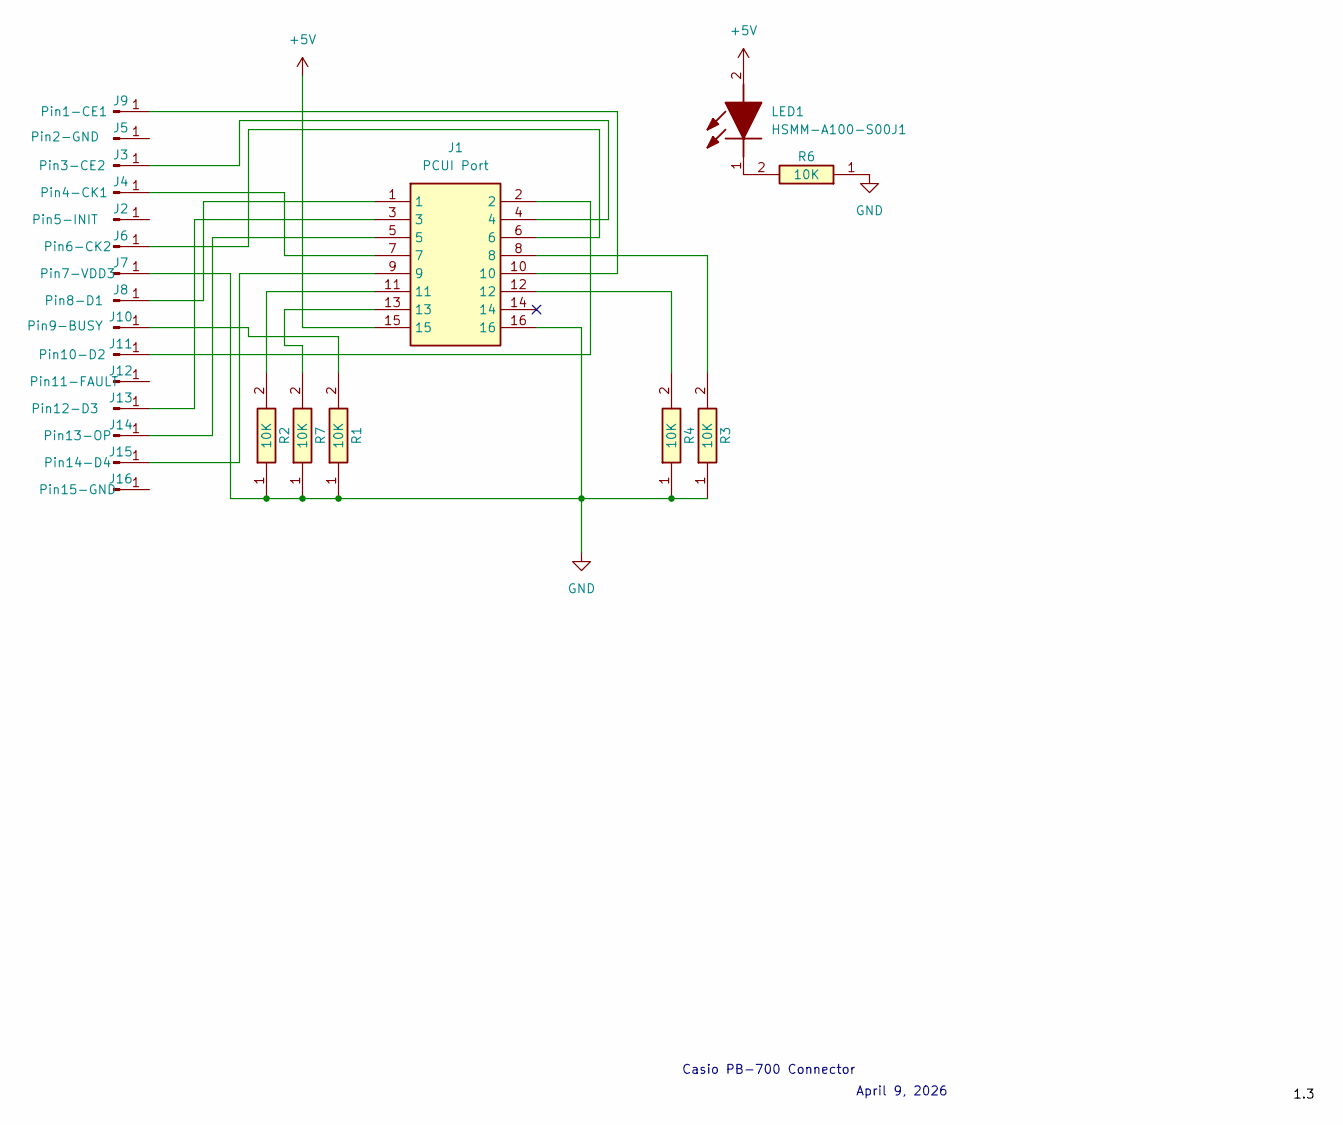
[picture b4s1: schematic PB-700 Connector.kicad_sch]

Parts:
J1: PCUI Port; TSS-108-XX-YYY-D; Manufacturer_Part_Number TSS-108-02-L-D
J2: Pin5-INIT; TH_1mm_1.5mm
J3: Pin3-CE2; TH_1mm_1.5mm
J4: Pin4-CK1; TH_1mm_1.5mm
J5: Pin2-GND; TH_1mm_1.5mm
J6: Pin6-CK2; TH_1mm_1.5mm
J7: Pin7-VDD3; TH_1mm_1.5mm
J8: Pin8-D1; TH_1mm_1.5mm
J9: Pin1-CE1; TH_1mm_1.5mm
J10: Pin9-BUSY; TH_1mm_1.5mm
J11: Pin10-D2; TH_1mm_1.5mm
J12: Pin11-FAULT; TH_1mm_1.5mm
J13: Pin12-D3; TH_1mm_1.5mm
J14: Pin13-OP; TH_1mm_1.5mm
J15: Pin14-D4; TH_1mm_1.5mm
J16: Pin15-GND; TH_1mm_1.5mm
LED1: HSMM-A100-S00J1; LEDM3528X200N; Mouser Part Number 630-HSMM-A100-S00J1
R1, R2, R3, R4, R6, R7: 10K; RESC2013X65N; Mouser Part Number 756-WCR0805-10KFI

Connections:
+5V: J1.15, LED1.2 (A)
GND: J1.16, J7.1, R1.1, R2.1, R3.1, R4.1, R6.1, R7.1
unnamed: J1.8, R3.2
unnamed: J1.11, R2.2
unnamed: J1.12, R4.2
unnamed: J1.13, R7.2
unnamed: J1.4, J3.1
unnamed: J1.7, J4.1
unnamed: J1.6, J6.1
unnamed: J1.1, J8.1
unnamed: J1.10, J9.1
unnamed: J10.1, R1.2
unnamed: J1.2, J11.1
unnamed: J1.3, J13.1
unnamed: J1.5, J14.1
unnamed: J1.9, J15.1
unnamed: LED1.1 (K), R6.2

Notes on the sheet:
April 9, 2026
Casio PB-700 Connector
